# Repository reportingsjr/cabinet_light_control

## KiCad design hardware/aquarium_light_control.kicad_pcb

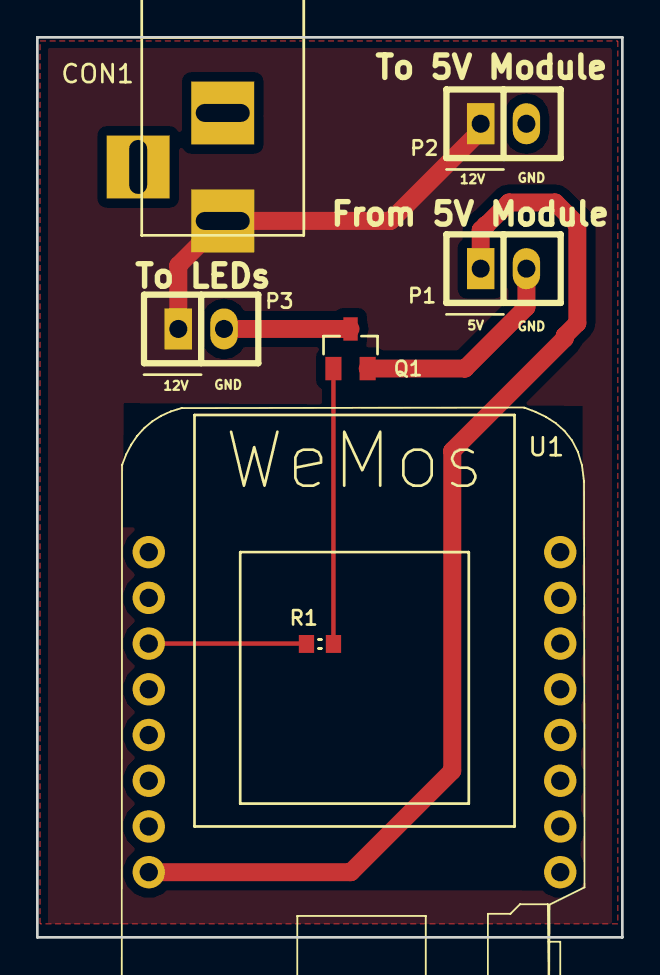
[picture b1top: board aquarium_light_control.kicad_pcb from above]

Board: 2 copper layers, 32.5 x 50.0 mm, 7 parts (0 on the bottom side), 6 nets.

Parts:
CON1: 5.5x2.5_BARREL_JACK; BARREL_JACK
P1: From_5V_Module; CONN-100MIL-M-1x2
P2: To_5V_Module; CONN-100MIL-M-1x2
P3: LED_POWER; CONN-100MIL-M-1x2
Q1: BSS806NE; SOT-23
R1: 1K; RESC1608X50
U1: WeMos_mini; D1_mini_board

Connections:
+5: P1.1, U1.1
+12: CON1.1, P2.1, P3.1
/Q_Gate: R1.2, U1.6
GND: CON1.2, CON1.3, P1.2, P2.2, Q1.2, U1.2
unnamed: P3.2, Q1.3
unnamed: Q1.1, R1.1

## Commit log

2016-11-27 Initial hardware rev and some example firmware.
2016-11-27 Added code to fetch the current time from NTP.
2016-11-27 Split web server code out of the setup function.
2016-12-05 Add code to fade light on and off throughout the day. The time period is currently hardcoded as a demo.
2016-12-05 Added an http page to toggle the lights on and off if need be.
2017-06-20 Create cabint light control based off of the aquarium lights.
2017-06-20 Remove files that are not used with the cabinet lights.
2017-08-20 Start adding some code to use a pushbutton to control the lights.
2017-09-09 Split firmware in to two. One for the main lights with the PIR sensor/manual button and one for lights that are purely slave lights. Added some button intelligence so it is intuitive to manual adjust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
2017-09-09 Remove old firmware directory
2017-09-09 Clean up slave lights firmware so it does not have code for the PIR sensor or pushbutton.
2017-09-09 Remove some crufty earlier attempts to control the slave lights from the master. I also removed use of String from the slave lights in an attempt to increase the performance of the slave lights. It d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
2017-09-10 The lights are working better through some code ugliness. I should come back through and clean up some of what I added in the commit. :)
